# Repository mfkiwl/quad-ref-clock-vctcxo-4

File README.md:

Quad reference clock
====================

TODO

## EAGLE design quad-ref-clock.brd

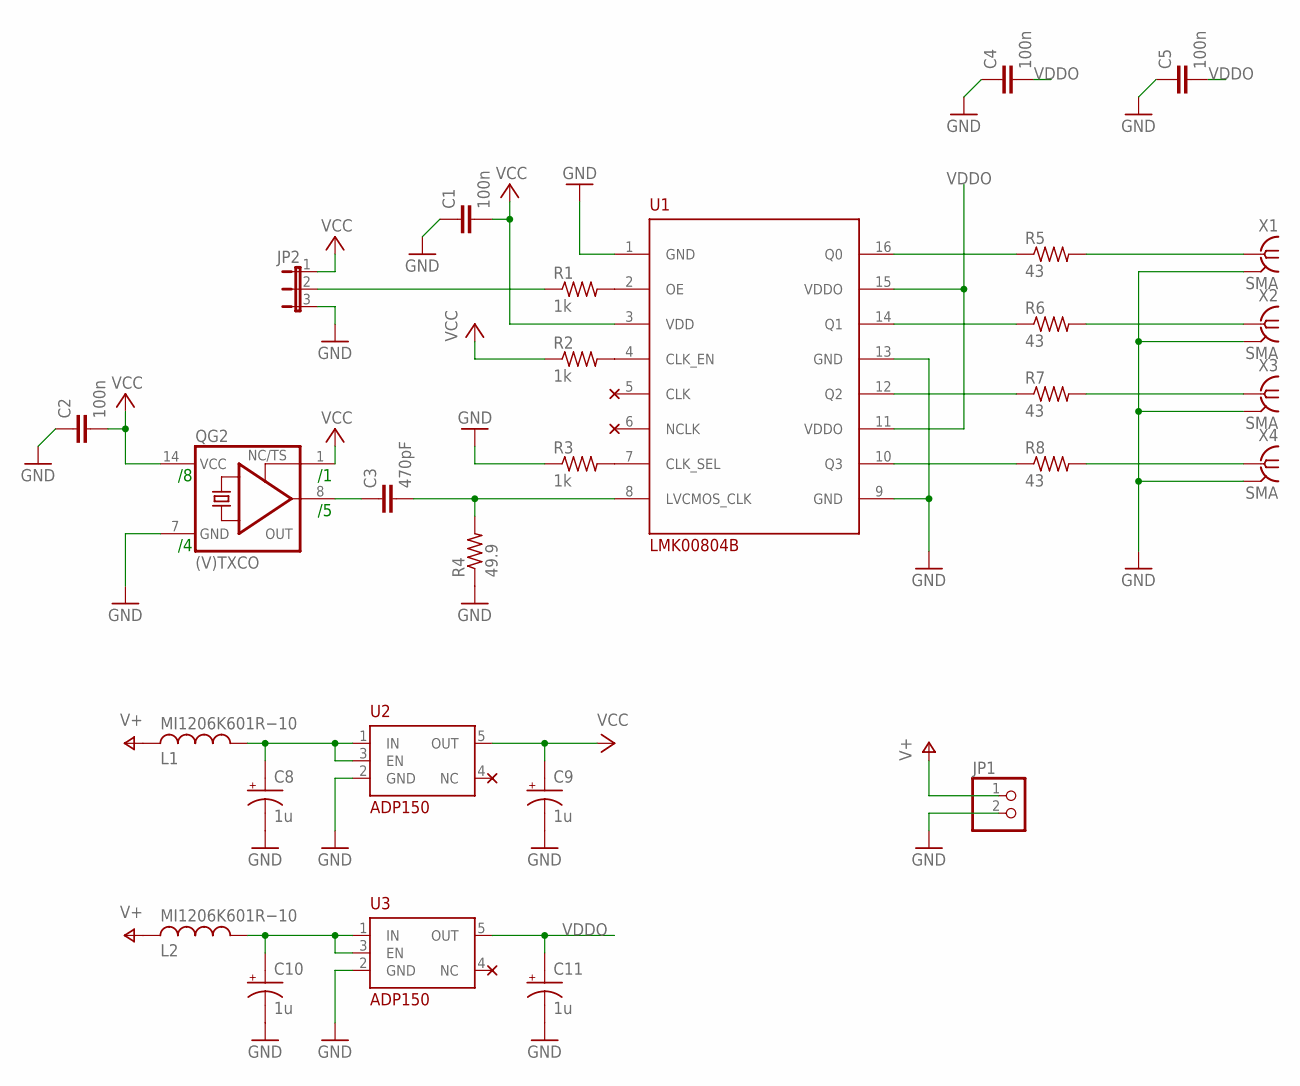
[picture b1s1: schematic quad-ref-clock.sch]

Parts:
C1, C2, C4, C5: 100n; C0805
C3: 470pF; C0805
C8, C9, C10, C11: 1u; CAPACITOR_POL_1210
JP1: PINHD-1X2; 1X02
JP2: JP2E; JP2
L1, L2: MI1206K601R−10; L3216C
QG2: (V)TXCO; DIL14S
R1, R2, R3: 1k; R0805
R4: 49.9; R0603
R5, R6, R7, R8: 43; R0603
U1: LMK00804B
U2, U3: ADP150; TSOT-23-5
X1, X2, X3, X4: SMA; J502-ND-142-0711-881/886

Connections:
C2: C8.A, L1.1, U2.1 (IN), U2.3 (EN)
GND: C1.1, C2.1, C4.1, C5.1, C8.C, C9.C, C10.C, C11.C, JP1.2, JP2.3, QG2.7 (GND), R3.1, R4.1, U1.1 (GND), U1.9 (GND), U1.13 (GND), U2.2 (GND), U3.2 (GND), X1.G@1 (2), X1.G@2 (2), X1.G@3 (2), X1.G@4 (2), X2.G@1 (2), X2.G@2 (2), X2.G@3 (2), X2.G@4 (2), X3.G@1 (2), X3.G@2 (2), X3.G@3 (2), X3.G@4 (2), X4.G@1 (2), X4.G@2 (2), X4.G@3 (2), X4.G@4 (2)
unnamed: R5.1, U1.16 (Q0)
unnamed: R6.1, U1.14 (Q1)
unnamed: R7.1, U1.12 (Q2)
unnamed: R8.1, U1.10 (Q3)
unnamed: R2.2, U1.4 (CLK_EN)
unnamed: R1.2, U1.2 (OE)
unnamed: C3.2, R4.2, U1.8 (LVCMOS_CLK)
unnamed: R3.2, U1.7 (CLK_SEL)
unnamed: R5.2, X1.1
unnamed: R6.2, X2.1
unnamed: R7.2, X3.1
unnamed: R8.2, X4.1
unnamed: C3.1, QG2.8 (OUT)
unnamed: JP2.2, R1.1
unnamed: C10.A, L2.1, U3.1 (IN), U3.3 (EN)
V+: JP1.1, L1.2, L2.2
VCC: C1.2, C2.2, C9.A, JP2.1, QG2.1 (TS), QG2.14 (VCC), R2.1, U1.3 (VDD), U2.5 (OUT)
VDDO: C4.2, C5.2, C11.A, U1.11 (VDDO), U1.15 (VDDO), U3.5 (OUT)

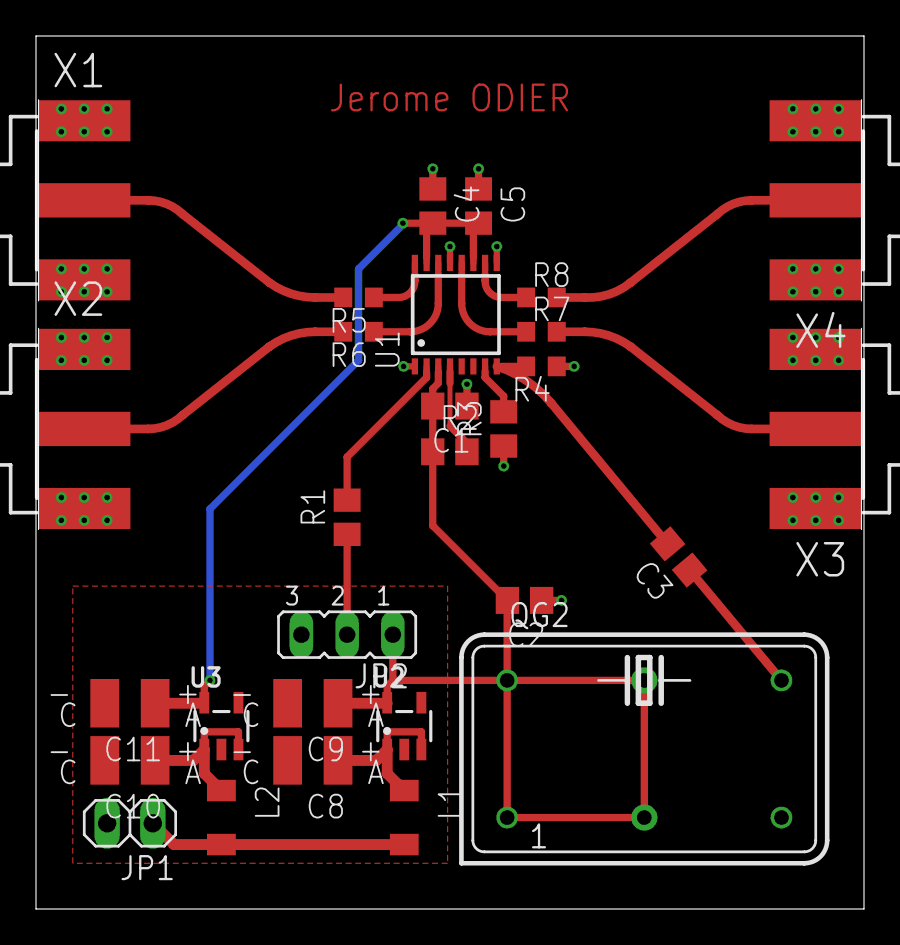
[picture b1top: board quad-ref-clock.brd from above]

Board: 2 copper layers, 46.0 x 48.5 mm, 29 parts (0 on the bottom side), 20 nets.
